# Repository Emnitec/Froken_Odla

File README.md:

# Froken_Odla
Fröken Ödla is a version of the Soughtable effect pedal Lizzard Queen.

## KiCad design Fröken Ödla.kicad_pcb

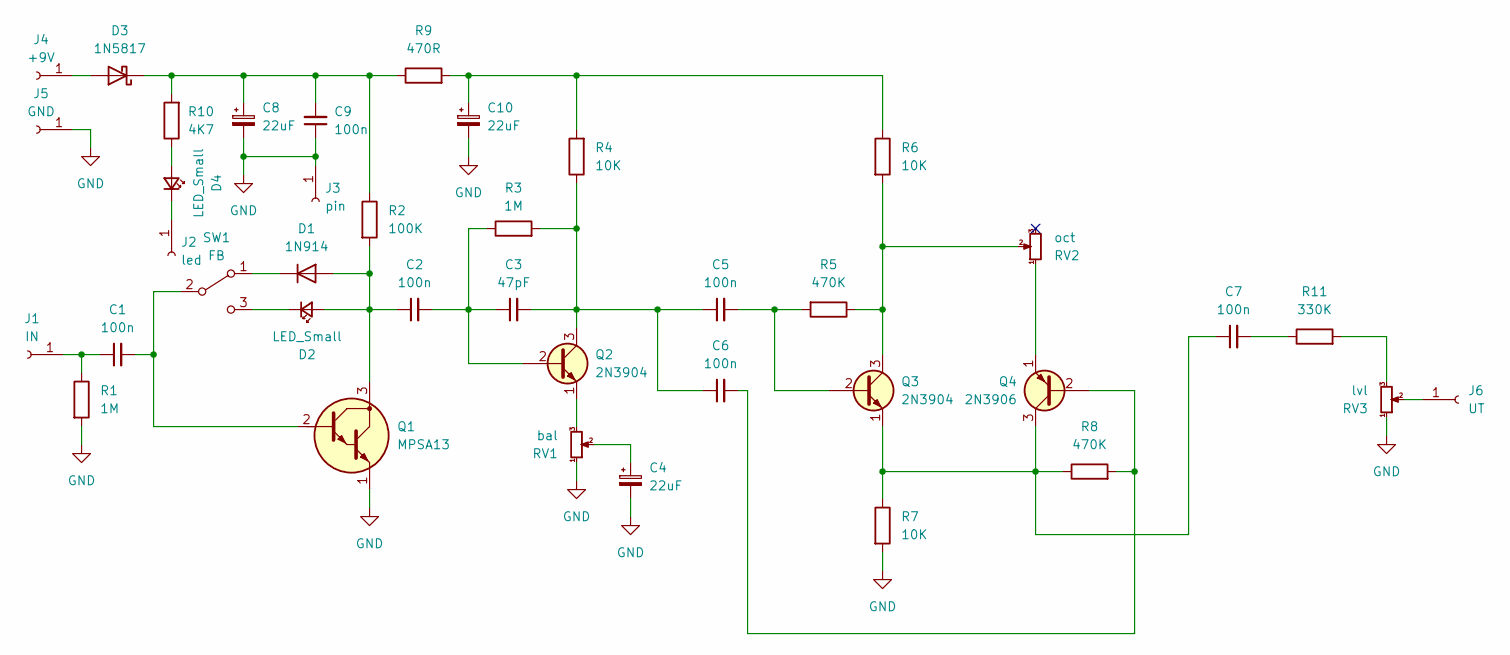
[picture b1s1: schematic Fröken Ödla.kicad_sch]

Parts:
C1, C2, C5, C6, C7, C9: 100n; C_Rect_L7.2mm_W2.5mm_P5.00mm_FKS2_FKP2_MKS2_MKP2
C3: 47pF; C_Disc_D3.0mm_W1.6mm_P2.50mm
C4, C8, C10: 22uF; CP_Radial_D5.0mm_P2.00mm
D1: 1N914; D_DO-35_SOD27_P7.62mm_Horizontal
D2, D4: LED_Small; SolderWire-0.5sqmm_1x02_P4.6mm_D0.9mm_OD2.1mm
D3: 1N5817; D_DO-41_SOD81_P10.16mm_Horizontal
J1: IN; SolderWire-0.5sqmm_1x01_D0.9mm_OD2.1mm
J2: led; SolderWire-0.5sqmm_1x01_D0.9mm_OD2.1mm
J3: pin; SolderWire-0.5sqmm_1x01_D0.9mm_OD2.1mm
J4: +9V; SolderWire-0.5sqmm_1x01_D0.9mm_OD2.1mm
J5: GND; SolderWire-0.5sqmm_1x01_D0.9mm_OD2.1mm
J6: UT; SolderWire-0.5sqmm_1x01_D0.9mm_OD2.1mm
Q1: MPSA13; TO-92_Inline_Wide_EBC
Q2, Q3: 2N3904; TO-92_Inline_Wide_EBC
Q4: 2N3906; TO-92_Inline_Wide_EBC
R1, R3: 1M; R_Axial_DIN0207_L6.3mm_D2.5mm_P7.62mm_Horizontal
R2: 100K; R_Axial_DIN0207_L6.3mm_D2.5mm_P7.62mm_Horizontal
R4, R6, R7: 10K; R_Axial_DIN0207_L6.3mm_D2.5mm_P7.62mm_Horizontal
R5, R8: 470K; R_Axial_DIN0207_L6.3mm_D2.5mm_P7.62mm_Horizontal
R9: 470R; R_Axial_DIN0207_L6.3mm_D2.5mm_P7.62mm_Horizontal
R10: 4K7; R_Axial_DIN0207_L6.3mm_D2.5mm_P7.62mm_Horizontal
R11: 330K; R_Axial_DIN0207_L6.3mm_D2.5mm_P7.62mm_Horizontal
RV1: bal; SolderWire-0.5sqmm_1x03_P4.6mm_D0.9mm_OD2.1mm
RV2: oct; SolderWire-0.5sqmm_1x03_P4.6mm_D0.9mm_OD2.1mm
RV3: lvl; SolderWire-0.5sqmm_1x03_P4.6mm_D0.9mm_OD2.1mm
SW1: FB; SolderWire-0.5sqmm_1x03_P4.6mm_D0.9mm_OD2.1mm

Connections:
GND: C4.2, C8.2, C9.1, C10.2, J3.1, J5.1, Q1.1 (E), R1.2, R7.2, RV1.1, RV3.1
unnamed: C4.1, RV1.2
unnamed: C7.2, R11.1
unnamed: C10.1, R4.2, R6.1, R9.2
unnamed: C2.1, D1.2 (A), D2.2 (A), Q1.3 (C), R2.2
unnamed: D1.1 (K), SW1.1 (A)
unnamed: D2.1 (K), SW1.3 (C)
unnamed: D3.2 (A), J4.1
unnamed: C8.1, C9.2, D3.1 (K), R2.1, R9.1, R10.2
unnamed: D4.2 (A), R10.1
unnamed: D4.1 (K), J2.1
unnamed: C1.1, J1.1, R1.1
unnamed: J6.1, RV3.2
unnamed: C1.2, Q1.2 (B), SW1.2 (B)
unnamed: C2.2, C3.1, Q2.2 (B), R3.1
unnamed: C3.2, C5.1, C6.1, Q2.3 (C), R3.2, R4.1
unnamed: Q2.1 (E), RV1.3
unnamed: C5.2, Q3.2 (B), R5.2
unnamed: Q3.3 (C), R5.1, R6.2, RV2.2
unnamed: C7.1, Q3.1 (E), Q4.3 (C), R7.1, R8.1
unnamed: C6.2, Q4.2 (B), R8.2
unnamed: Q4.1 (E), RV2.1
unnamed: R11.2, RV3.3

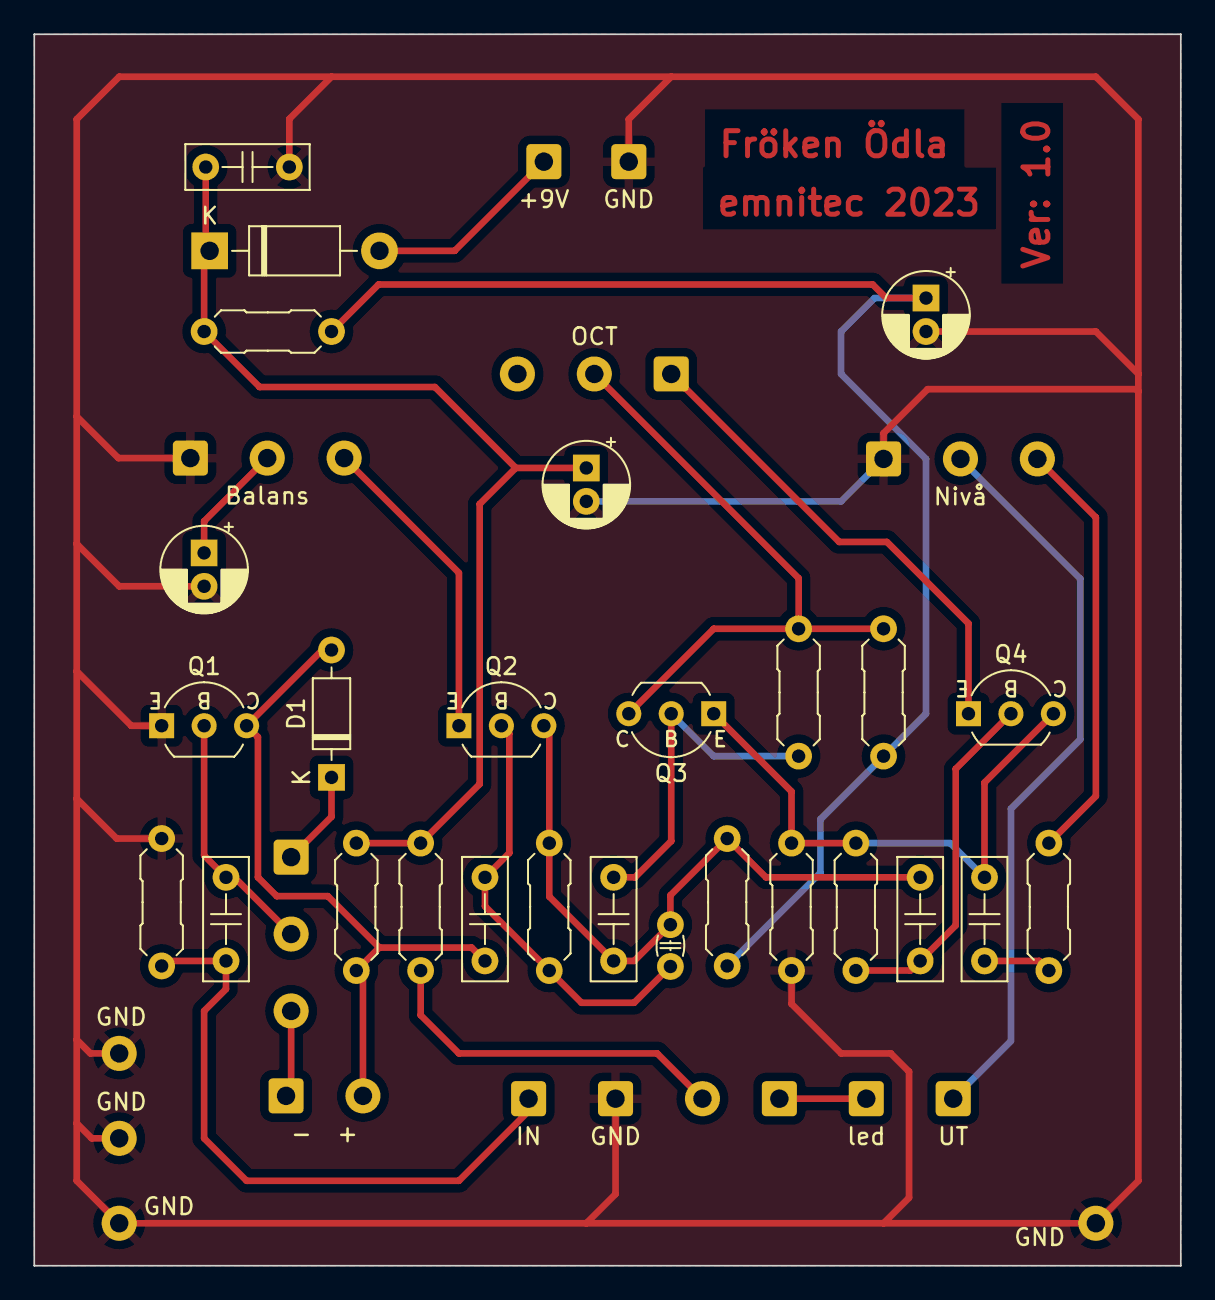
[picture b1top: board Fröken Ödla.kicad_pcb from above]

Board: 2 copper layers, 68.6 x 73.7 mm, 39 parts (0 on the bottom side), 23 nets.
